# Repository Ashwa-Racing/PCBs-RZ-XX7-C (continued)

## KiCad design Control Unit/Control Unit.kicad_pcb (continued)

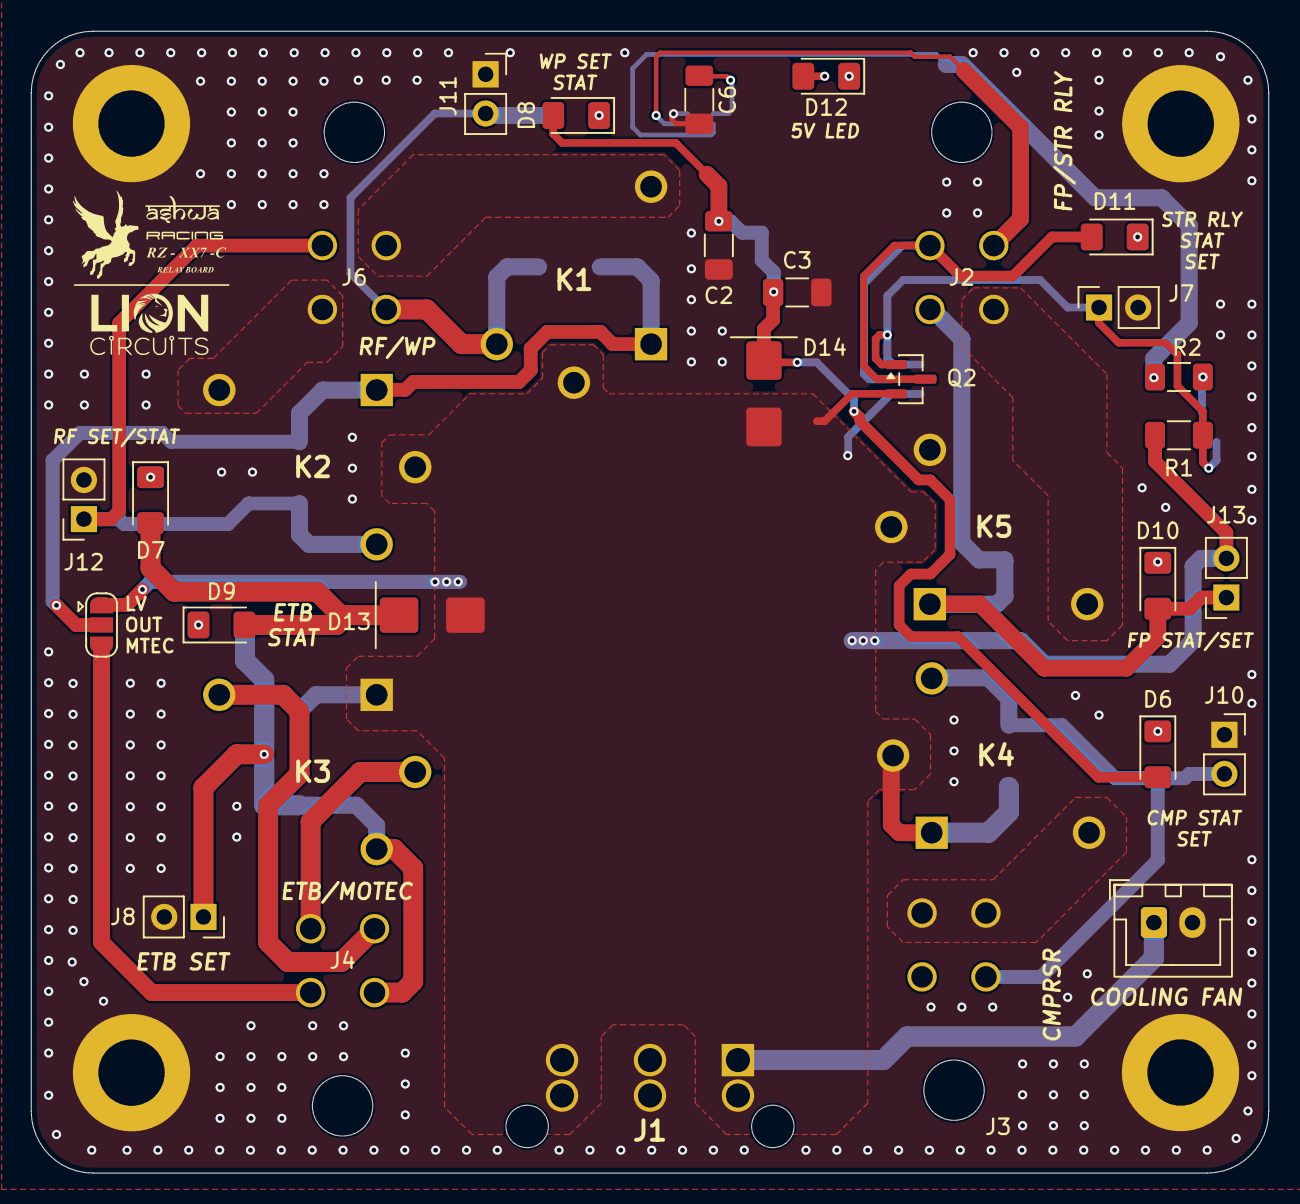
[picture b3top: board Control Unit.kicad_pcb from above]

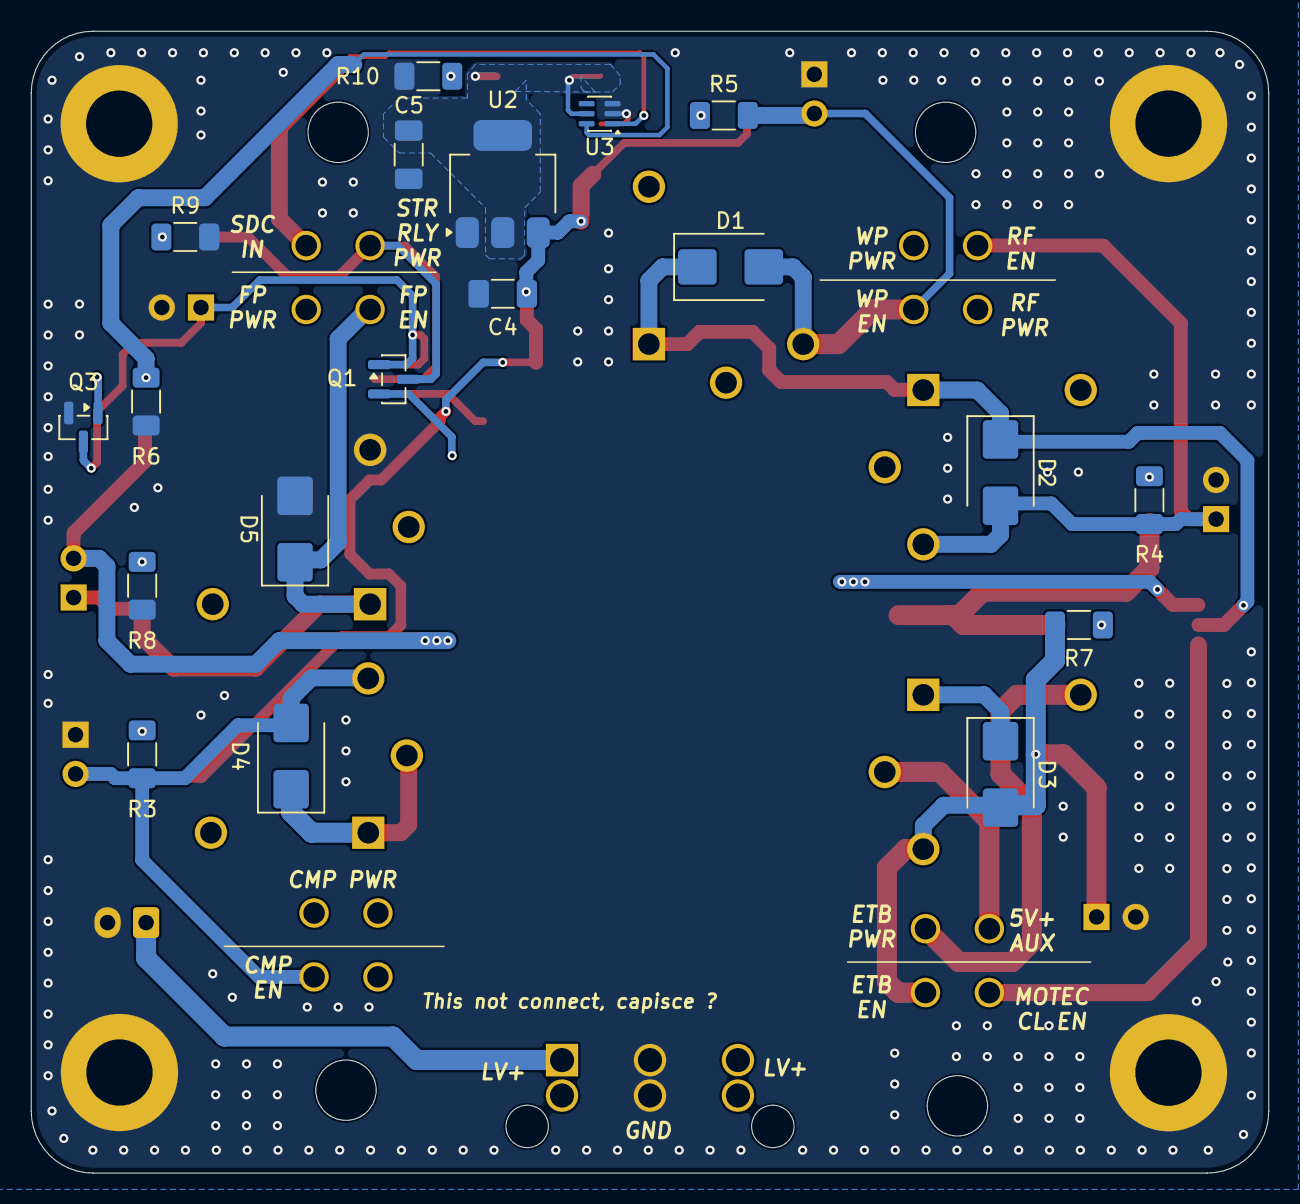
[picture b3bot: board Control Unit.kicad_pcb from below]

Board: 2 copper layers, 80.2 x 74.0 mm, 56 parts (19 on the bottom side), 30 nets.

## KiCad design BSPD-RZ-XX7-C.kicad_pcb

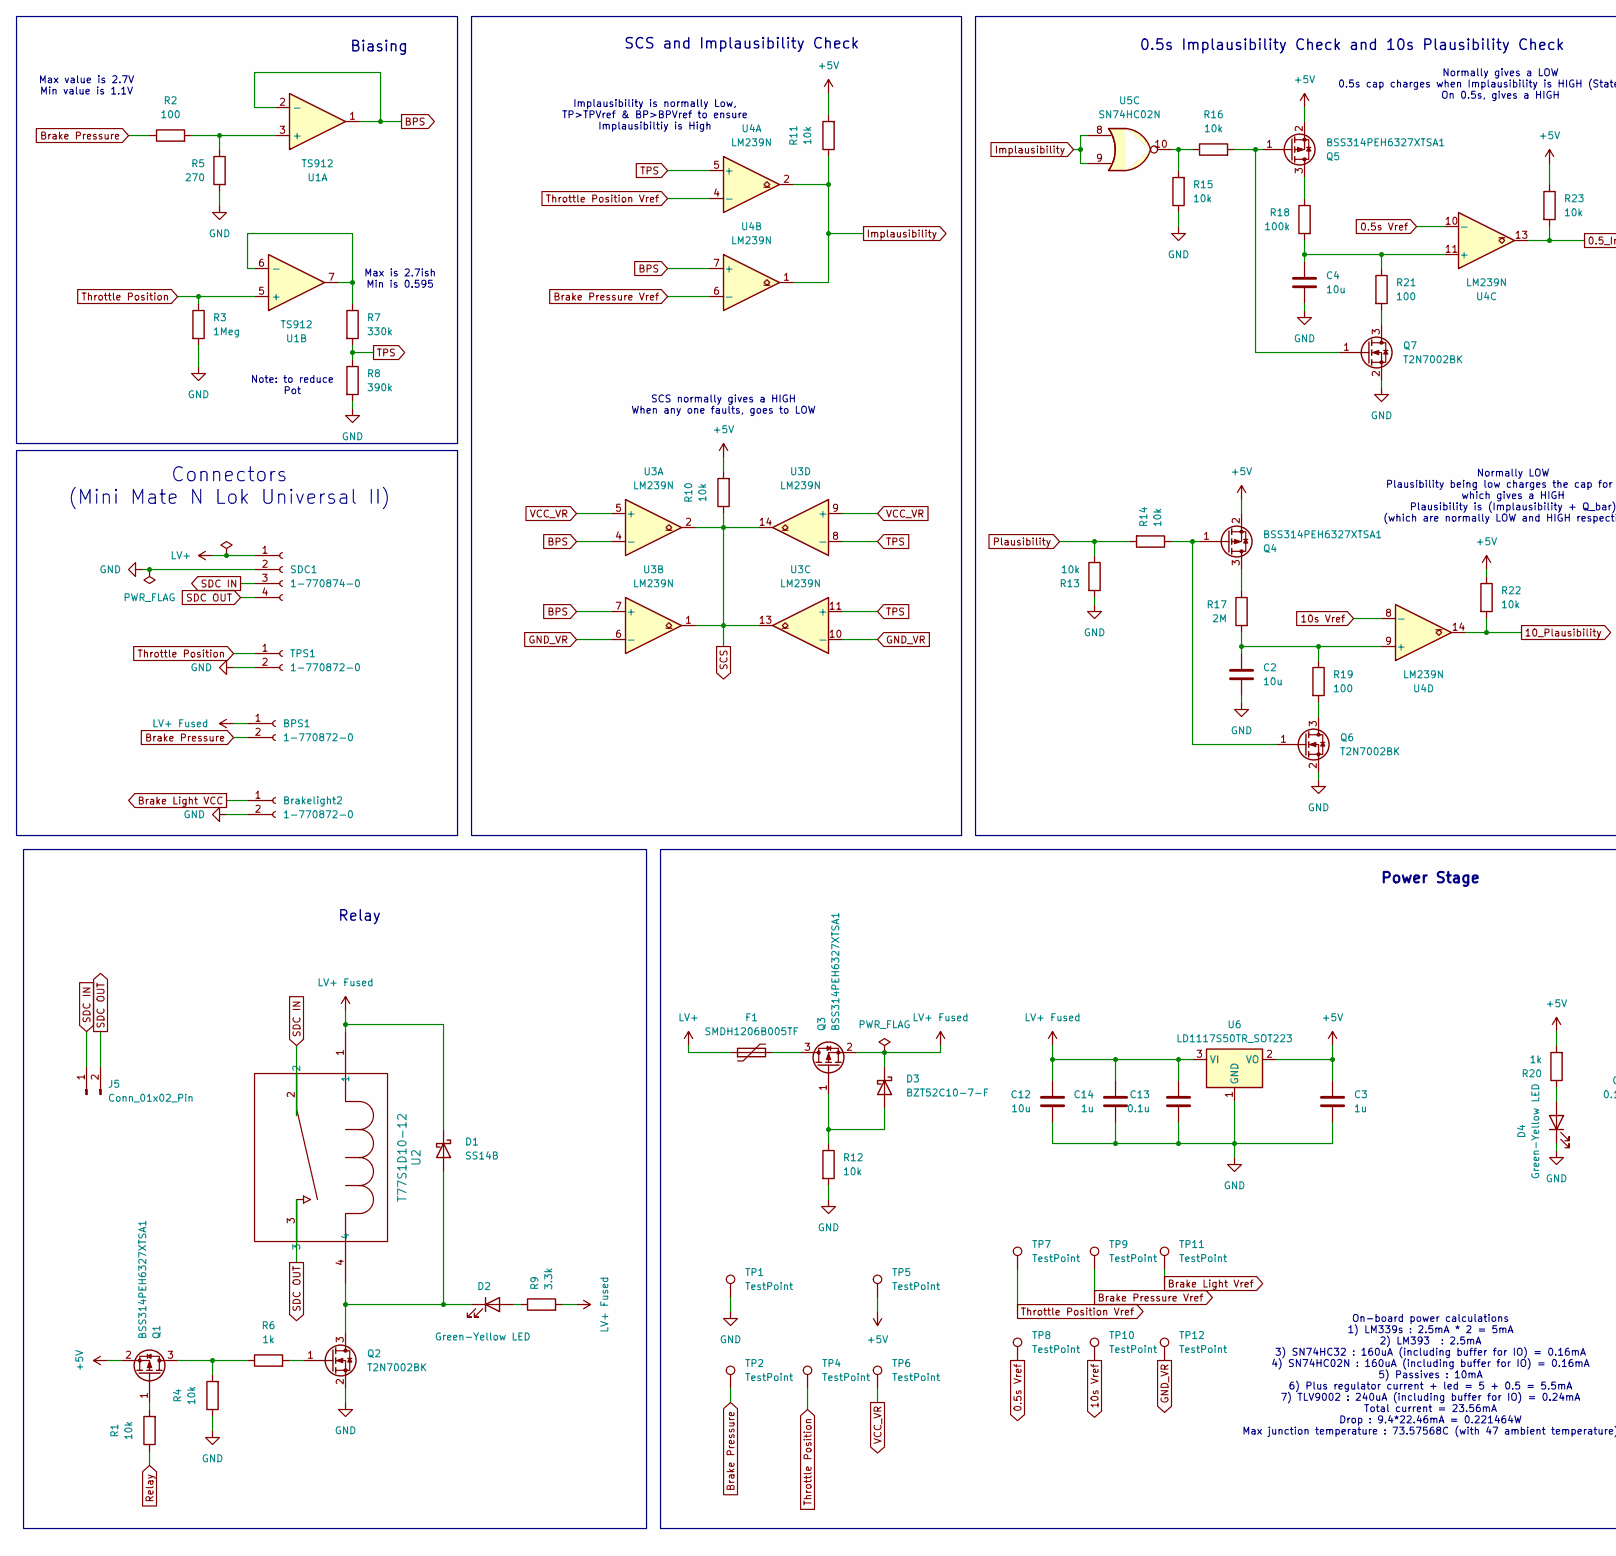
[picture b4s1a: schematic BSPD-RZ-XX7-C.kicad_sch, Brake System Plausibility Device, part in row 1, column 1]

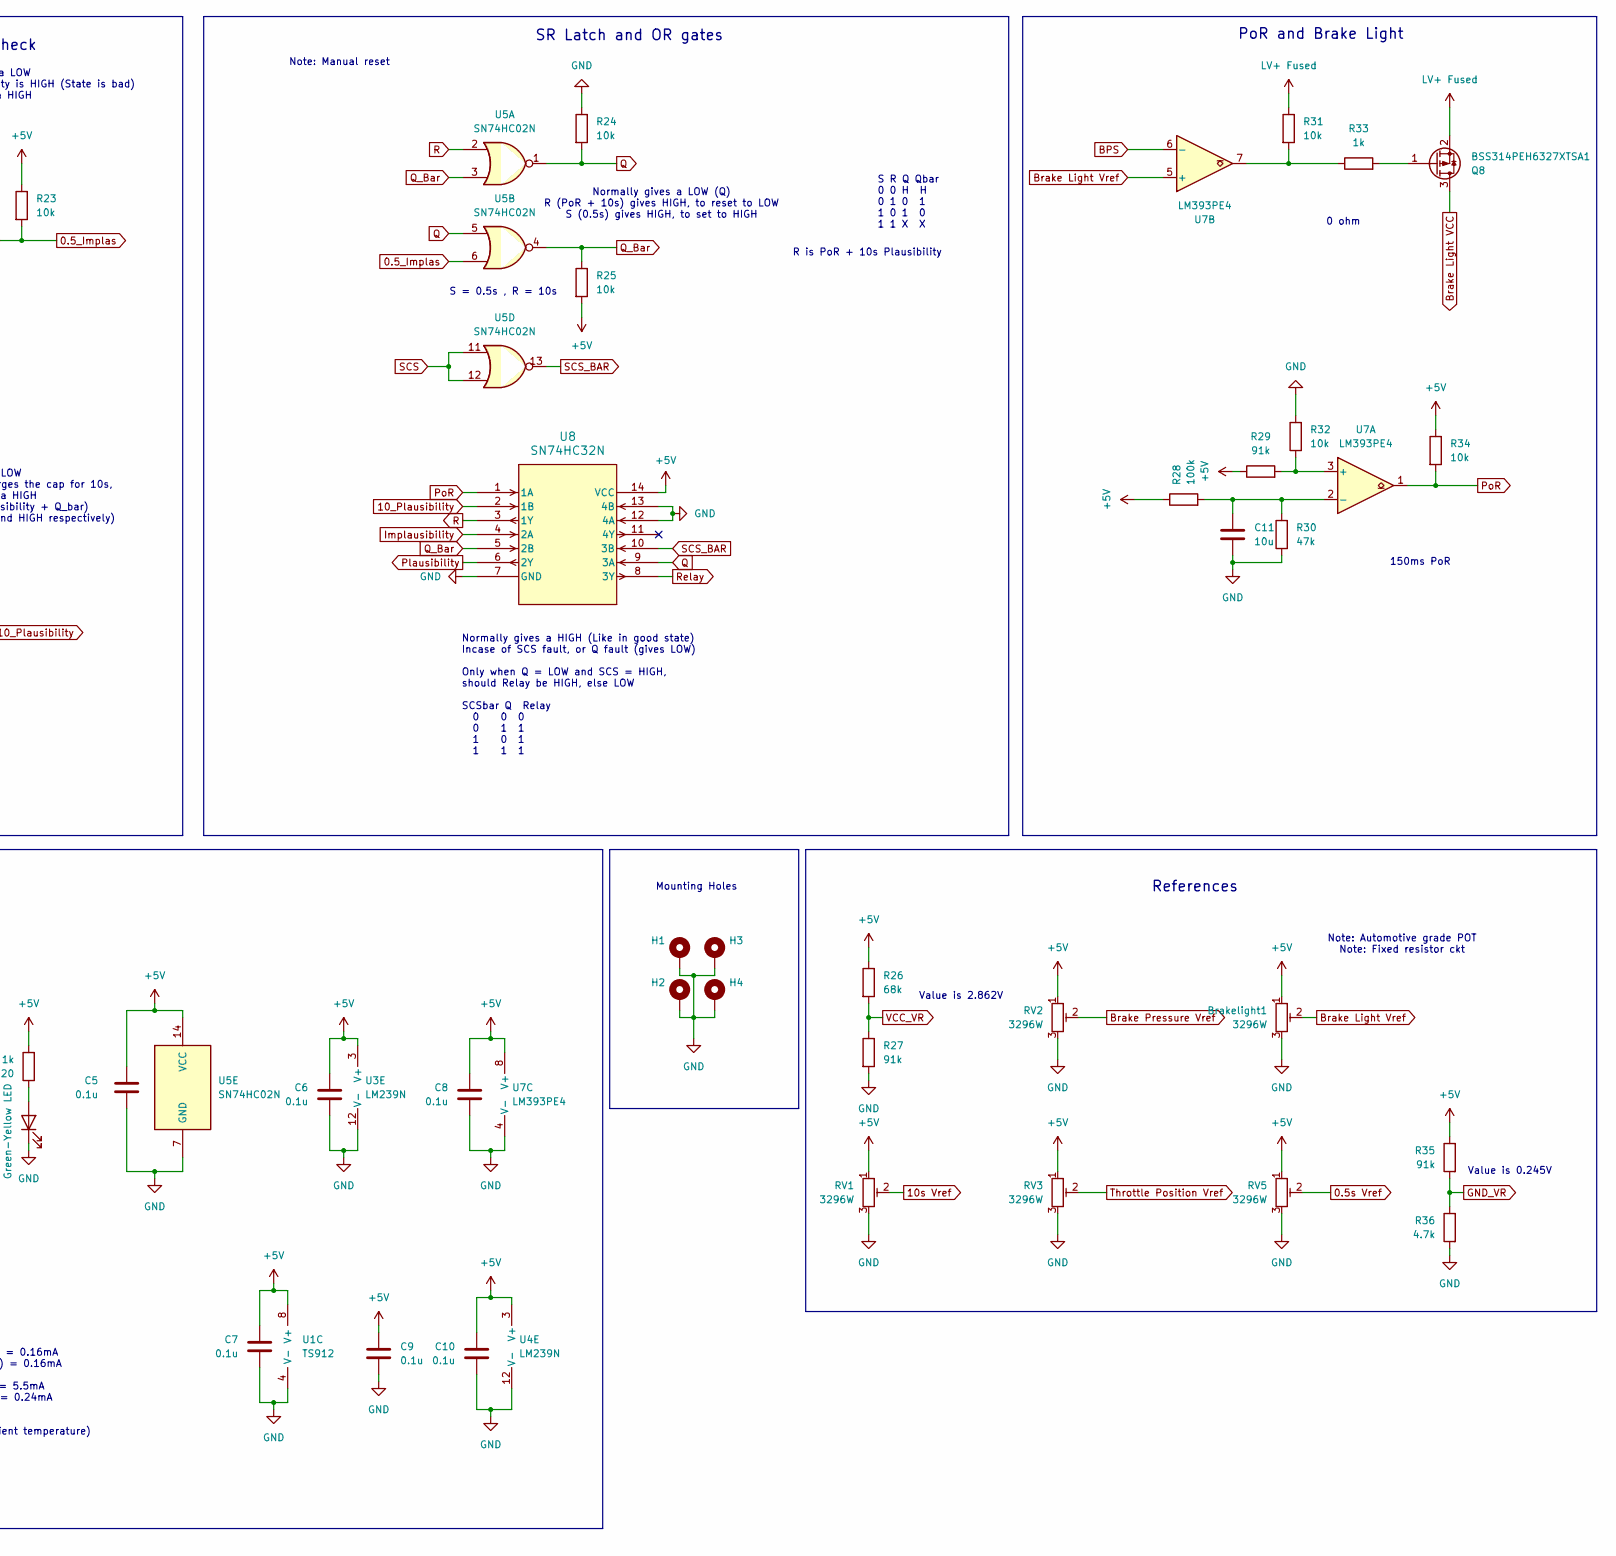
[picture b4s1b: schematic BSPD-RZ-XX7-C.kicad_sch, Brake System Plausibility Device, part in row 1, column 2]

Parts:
BPS1: 1-770872-0; CON2_1X2_P163_VMNL-1MTG_TYC
Brakelight1: 3296W; Potentiometer_Bourns_3296W_Vertical
Brakelight2: 1-770872-0; CON2_1X2_P163_VMNL-1MTG_TYC
C2, C4, C11, C12: 10u; C_1206_3216Metric_Pad1.33x1.80mm_HandSolder
C3, C14: 1u; C_1206_3216Metric_Pad1.33x1.80mm_HandSolder
C5, C6, C7, C8, C9, C10, C13: 0.1u; C_1206_3216Metric_Pad1.33x1.80mm_HandSolder
D1: SS14B; D_SMB_Handsoldering
D2, D4: Green-Yellow LED; LED_1206_3216Metric_Pad1.42x1.75mm_HandSolder
D3: BZT52C10-7-F; Nexperia_CFP3_SOD-123W
F1: SMDH1206B005TF; Fuse_1206_3216Metric_Pad1.42x1.75mm_HandSolder
H1, H2, H3, H4: MountingHole_Pad; MountingHole_4.3mm_M4_ISO7380_Pad
J5: Conn_01x02_Pin; PinHeader_1x02_P2.54mm_Vertical
Q1, Q3, Q4, Q5, Q8: BSS314PEH6327XTSA1; SOT-23
Q2, Q6, Q7: T2N7002BK; SOT-23
R1, R4, R10, R11, R12, R13, R14, R15, R16, R22, R23, R24, R25, R31, R32, R34: 10k; R_1206_3216Metric_Pad1.30x1.75mm_HandSolder
R2, R19, R21: 100; R_1206_3216Metric_Pad1.30x1.75mm_HandSolder
R3: 1Meg; R_1206_3216Metric_Pad1.30x1.75mm_HandSolder
R5: 270; R_1206_3216Metric_Pad1.30x1.75mm_HandSolder
R6, R20, R33: 1k; R_1206_3216Metric_Pad1.30x1.75mm_HandSolder
R7: 330k; R_1206_3216Metric_Pad1.30x1.75mm_HandSolder
R8: 390k; R_1206_3216Metric_Pad1.30x1.75mm_HandSolder
R9: 3.3k; R_1206_3216Metric_Pad1.30x1.75mm_HandSolder
R17: 2M; R_1206_3216Metric_Pad1.30x1.75mm_HandSolder
R18, R28: 100k; R_1206_3216Metric_Pad1.30x1.75mm_HandSolder
R26: 68k; R_1206_3216Metric_Pad1.30x1.75mm_HandSolder
R27, R29, R35: 91k; R_1206_3216Metric_Pad1.30x1.75mm_HandSolder
R30: 47k; R_1206_3216Metric_Pad1.30x1.75mm_HandSolder
R36: 4.7k; R_1206_3216Metric_Pad1.30x1.75mm_HandSolder
RV1, RV2, RV3, RV5: 3296W; Potentiometer_Bourns_3296W_Vertical
SDC1: 1-770874-0; CONN4_1-770874-0_TEC
TP1, TP2, TP4, TP5, TP6, TP7, TP8, TP9, TP10, TP11, TP12: TestPoint; TestPoint_Pad_D2.5mm
TPS1: 1-770872-0; CON2_1X2_P163_VMNL-1MTG_TYC
U1: TS912; SOIC-8_3.9x4.9mm_P1.27mm
U2: T77S1D10-12; RELAY4-402X717_575
U3, U4: LM239N; DIP-14_W7.62mm_Socket
U5: SN74HC02N; DIP-14_W7.62mm_Socket
U6: LD1117S50TR_SOT223; SOT-223-3_TabPin2
U7: LM393PE4; DIP-8_W7.62mm_Socket
U8: SN74HC32N; DIP-14_W7.62mm_Socket

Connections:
0.5_Implas: R23.2, U4.13, U5.6
0.5s Vref: RV5.2, TP8.1 (1_1), U4.10 (-)
10_Plausibility: R22.2, U4.14, U8.2 (1B)
10s Vref: RV1.2, TP10.1 (1_1), U4.8 (-)
+5V: Brakelight1.1, C3.1, C5.1, C6.1, C7.1, C8.1, C9.1, C10.1, Q1.2 (S), Q4.2 (S), Q5.2 (S), R10.2, R11.2, R20.2, R22.1, R23.1, R25.2, R26.1, R28.1, R29.1, R34.1, R35.1, RV1.1, RV2.1, RV3.1, RV5.1, TP5.1 (1_1), U1.8 (V+), U3.3 (V+), U4.3 (V+), U5.14 (VCC), U6.2 (VO), U7.8 (V+), U8.14 (VCC)
BPS: U1.1, U1.2 (-), U3.4 (-), U3.7 (+), U4.7 (+), U7.6 (-)
Brake Light VCC: Brakelight2.1, Q8.3 (D)
Brake Light Vref: Brakelight1.2, TP11.1 (1_1), U7.5 (+)
Brake Pressure: BPS1.2, R2.1, TP2.1 (1_1)
Brake Pressure Vref: RV2.2, TP9.1 (1_1), U4.6 (-)
GND: Brakelight1.3, Brakelight2.2, C2.2, C3.2, C4.2, C5.2, C6.2, C7.2, C8.2, C9.2, C10.2, C11.1, C12.2, C13.2, C14.2, D4.1 (K), H1.1 (1_1), H2.1 (1_1), H3.1 (1_1), H4.1 (1_1), Q2.2 (S), Q6.2 (S), Q7.2 (S), R3.2, R4.1, R5.2, R8.2, R12.2, R13.2, R15.1, R24.1, R27.2, R30.1, R32.2, R36.2, RV1.3, RV2.3, RV3.3, RV5.3, SDC1.2, TP1.1 (1_1), TPS1.2, U1.4 (V-), U3.12 (V-), U4.12 (V-), U5.7 (GND), U6.1 (GND), U7.4 (V-), U8.7 (GND), U8.12 (4A), U8.13 (4B)
GND_VR: R35.2, R36.1, TP12.1 (1_1), U3.6 (-), U3.10 (-)
Implausibility: R11.1, U4.1, U4.2, U5.8, U5.9, U8.4 (2A)
LV+: F1.1, SDC1.1
LV+ Fused: BPS1.1, C12.1, C13.1, C14.1, D1.1 (K), D3.1 (K), Q3.2 (S), Q8.2 (S), R9.2, R31.1, U2.1, U6.3 (VI)
unnamed: D1.2 (A), D2.1 (K), Q2.3 (D), U2.4
unnamed: D2.2 (A), R9.1
unnamed: D3.2 (A), Q3.1 (G), R12.1
unnamed: D4.2 (A), R20.1
unnamed: Q1.3 (D), R4.2, R6.1
unnamed: Q1.1 (G), R1.2
unnamed: Q2.1 (G), R6.2
unnamed: F1.2, Q3.3 (D)
unnamed: Q4.3 (D), R17.1
unnamed: Q4.1 (G), Q6.1 (G), R14.1
unnamed: Q5.3 (D), R18.1
unnamed: Q5.1 (G), Q7.1 (G), R16.2
unnamed: Q6.3 (D), R19.2
unnamed: Q7.3 (D), R21.2
unnamed: Q8.1 (G), R33.2
unnamed: R15.2, R16.1, U5.10
unnamed: R31.2, R33.1, U7.7
unnamed: R2.2, R5.1, U1.3 (+)
unnamed: R7.1, U1.6 (-), U1.7
unnamed: C4.1, R18.2, R21.1, U4.11 (+)
unnamed: C2.1, R17.2, R19.1, U4.9 (+)
unnamed: R29.2, R32.1, U7.3 (+)
unnamed: C11.2, R28.2, R30.2, U7.2 (-)
Plausibility: R13.1, R14.2, U8.6 (2Y)
PoR: R34.2, U7.1, U8.1 (1A)
Q: R24.2, U5.1, U5.5, U8.9 (3A)
Q_Bar: R25.1, U5.3, U5.4, U8.5 (2B)
R: U5.2, U8.3 (1Y)
Relay: R1.1, U8.8 (3Y)
SCS: R10.1, U3.1, U3.2, U3.13, U3.14, U5.11, U5.12
SCS_BAR: U5.13, U8.10 (3B)
SDC IN: J5.1, SDC1.3, U2.2
SDC OUT: J5.2, SDC1.4, U2.3
TPS: R7.2, R8.1, U3.8 (-), U3.11 (+), U4.5 (+)
Throttle Position: R3.1, TP4.1 (1_1), TPS1.1, U1.5 (+)
Throttle Position Vref: RV3.2, TP7.1 (1_1), U4.4 (-)
VCC_VR: R26.2, R27.1, TP6.1 (1_1), U3.5 (+), U3.9 (+)

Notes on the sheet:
Normally LOW Plausibility being low charges the cap for 10s, which gives a HIGH Plausibility is (Implausibility + Q_bar) (which are normally LOW and HIGH respectively)
Normally gives a LOW (Q) R (PoR + 10s) gives HIGH, to reset to LOW S (0.5s) gives HIGH, to set to HIGH
Normally gives a LOW 0.5s cap charges when Implausibility is HIGH (State is bad) On 0.5s, gives a HIGH
SR Latch and OR gates
On-board power calculations 1) LM339s : 2.5mA * 2 = 5mA 2) LM393 : 2.5mA 3) SN74HC32 : 160uA (including buffer for IO) = 0.16mA 4) SN74HC02N : 160uA (including buffer for IO) = 0.16mA 5) Passives : 10mA 6) Plus regulator current + led = 5 + 0.5 = 5.5mA 7) TLV9002 : 240uA (including buffer for IO) =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
Connectors (Mini Mate N Lok Universal II)
References
S = 0.5s , R = 10s
Relay
Value is 0.245V
SCS and Implausibility Check
Mounting Holes
150ms PoR
0 ohm
0.5s Implausibility Check and 10s Plausibility Check
S R Q Qbar 0 0 H H 0 1 0 1 1 0 1 0 1 1 X X
R is PoR + 10s Plausibility
Max value is 2.7V Min value is 1.1V
Implausibility is normally Low, TP>TPVref & BP>BPVref to ensure Implausibiltiy is High
Value is 2.862V
Biasing
PoR and Brake Light
Note: to reduce Pot
Normally gives a HIGH (Like in good state) Incase of SCS fault, or Q fault (gives LOW) Only when Q = LOW and SCS = HIGH, should Relay be HIGH, else LOW SCSbar Q Relay 0 0 0 0 1 1 1 0 1 1 1 1
SCS normally gives a HIGH When any one faults, goes to LOW
Note: Automotive grade POT Note: Fixed resistor ckt
Power Stage
Note: Manual reset
Max is 2.7ish Min is 0.595

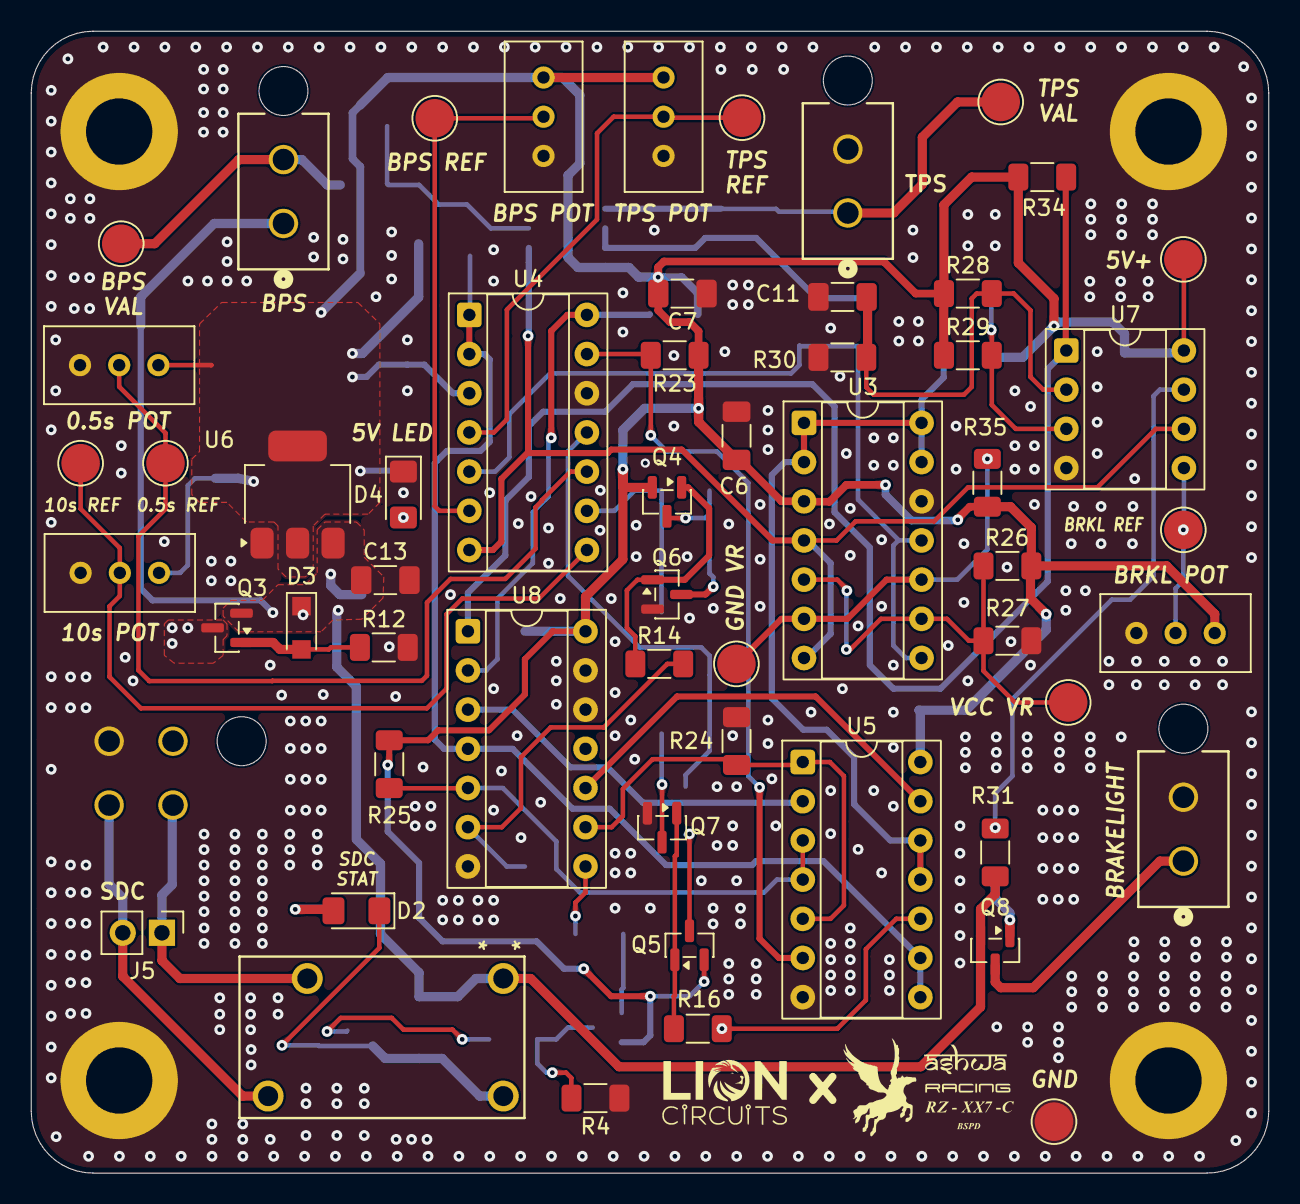
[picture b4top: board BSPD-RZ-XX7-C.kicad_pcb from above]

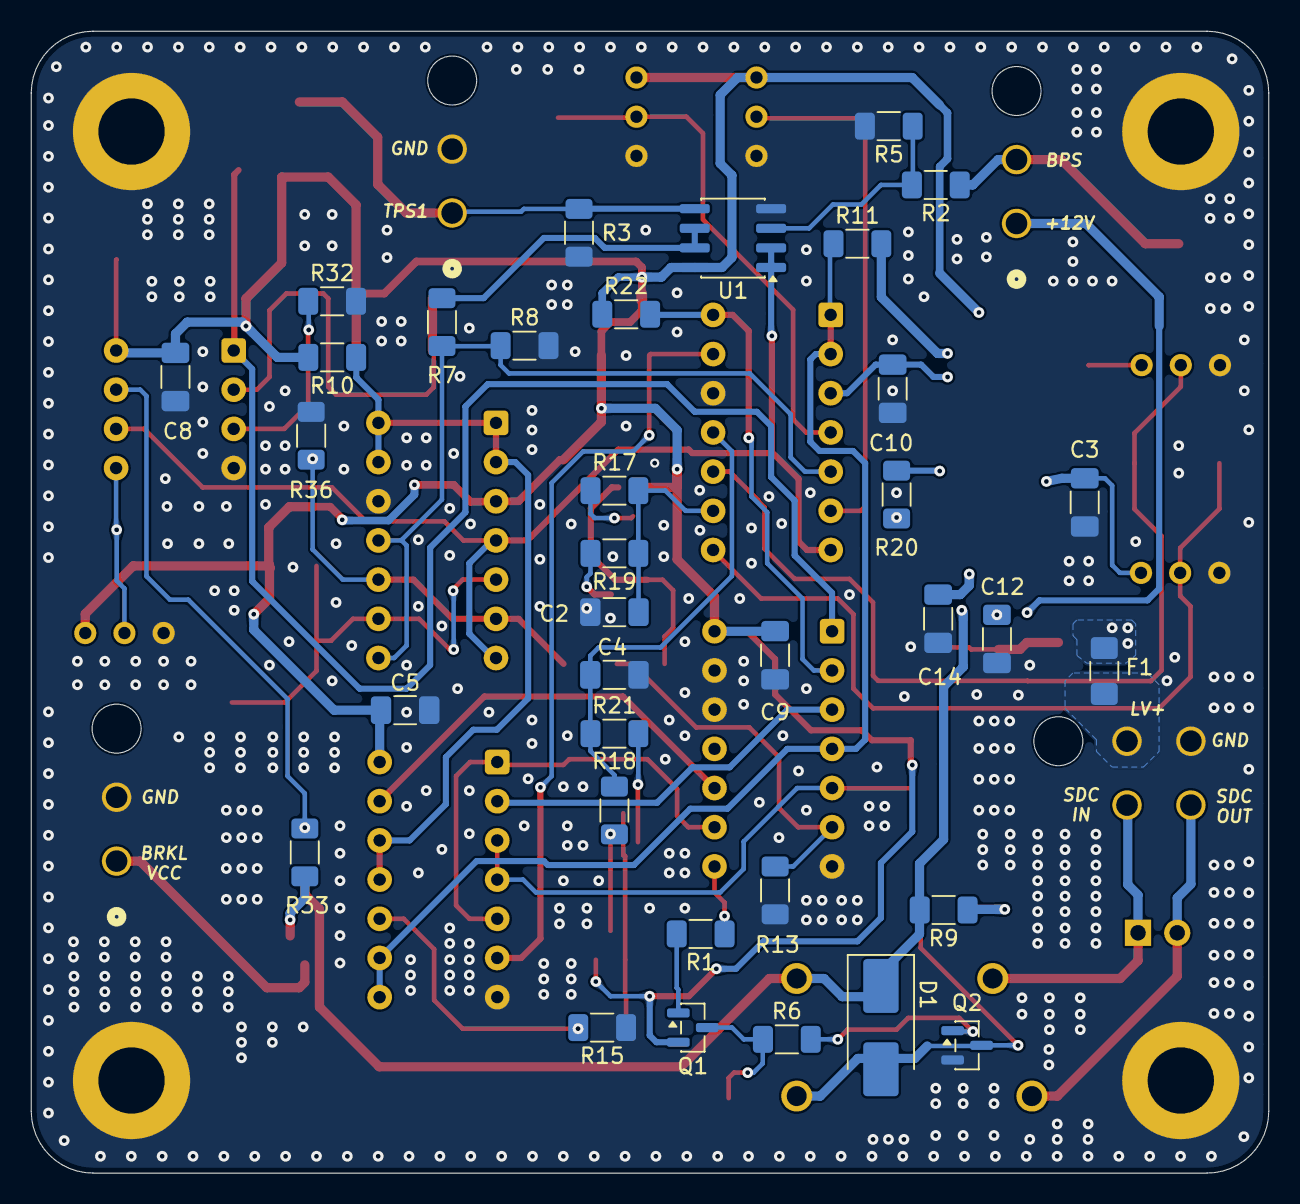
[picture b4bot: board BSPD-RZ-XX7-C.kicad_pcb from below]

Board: 2 copper layers, 80.2 x 74.0 mm, 95 parts (35 on the bottom side), 52 nets.
